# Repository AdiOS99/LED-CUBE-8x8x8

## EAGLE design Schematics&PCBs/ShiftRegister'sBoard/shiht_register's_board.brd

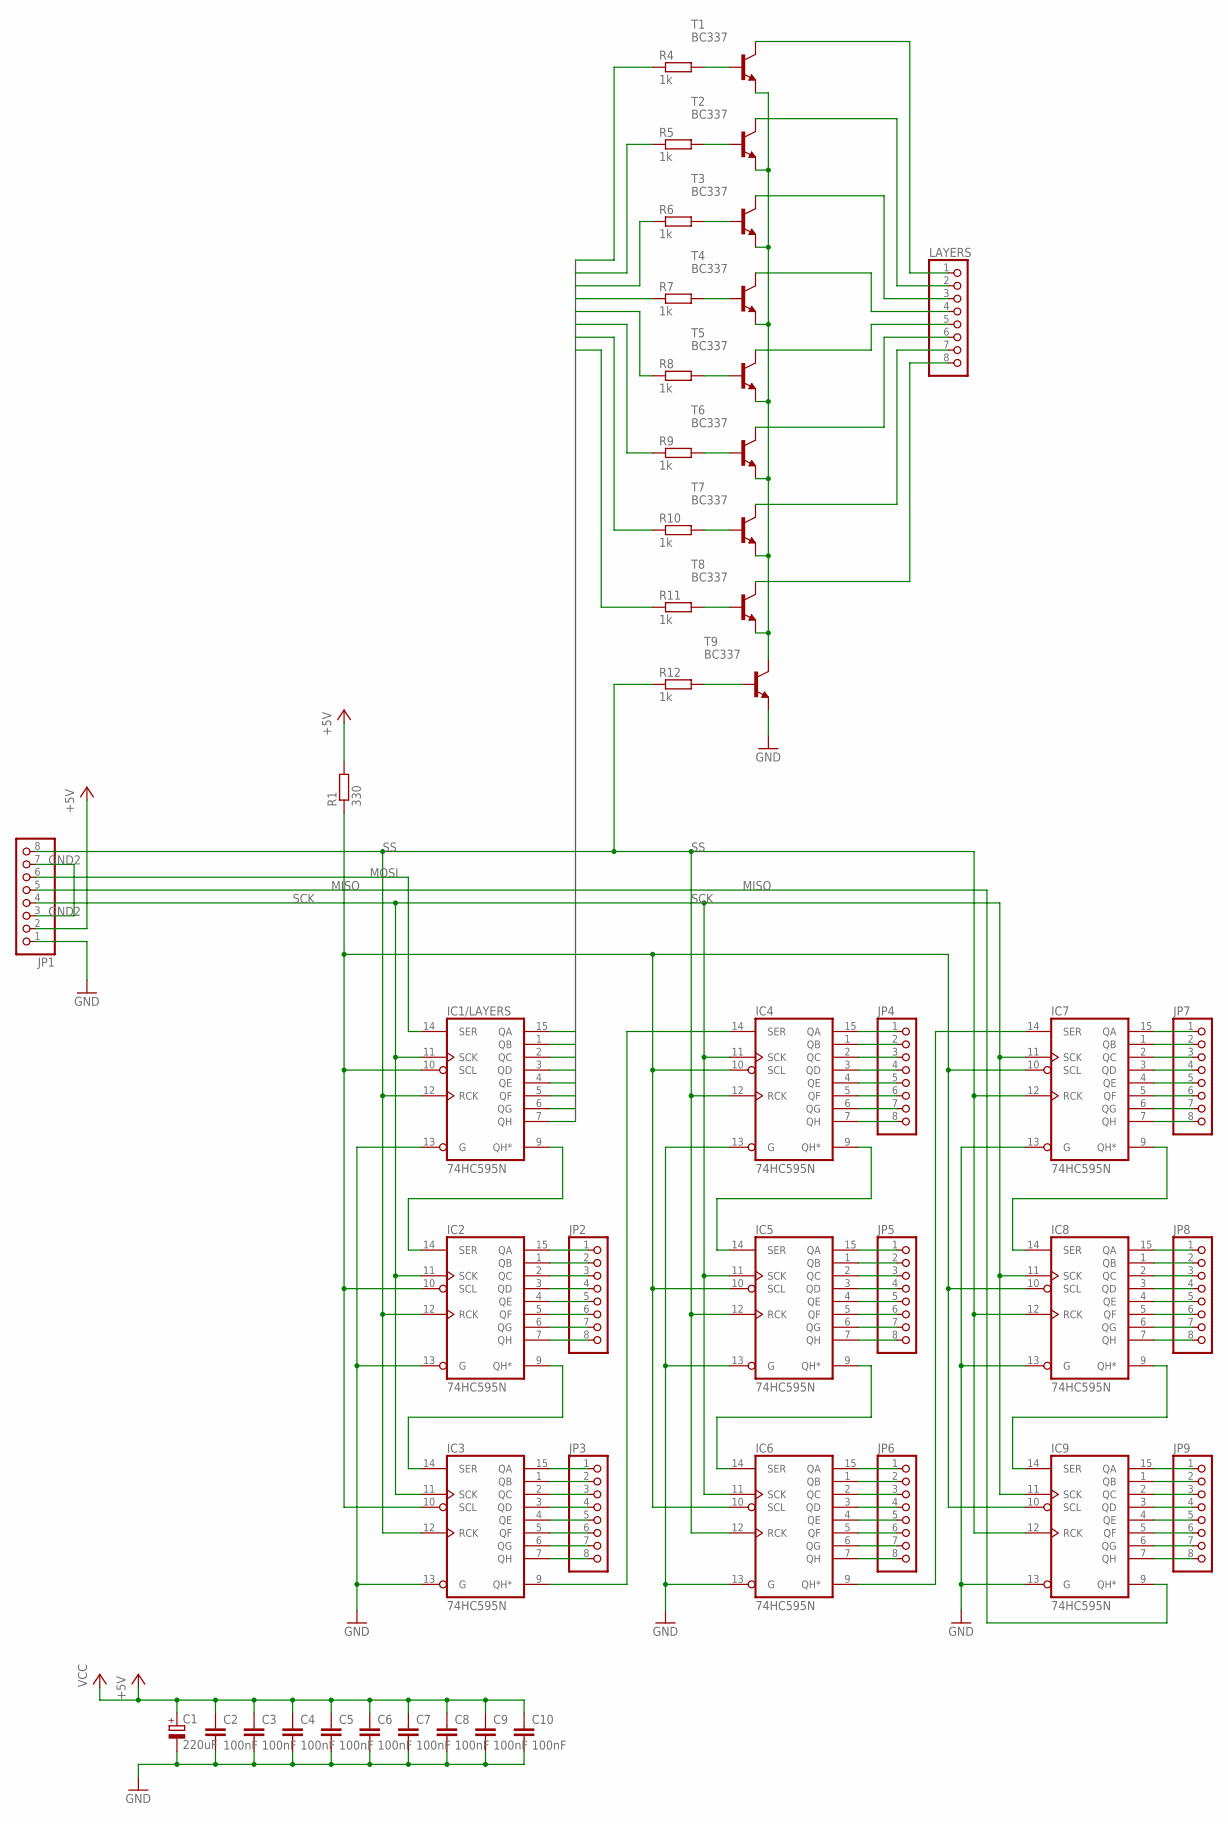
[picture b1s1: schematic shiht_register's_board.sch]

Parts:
C1: 220uF; E3,5-8
C2, C3, C4, C5, C6, C7, C8, C9, C10: 100nF; C025-025X050
IC1/LAYERS, IC2, IC3, IC4, IC5, IC6, IC7, IC8, IC9: 74HC595N; DIL16
JP1, JP2, JP3, JP4, JP5, JP6, JP7, JP8, JP9: PINHD-1X8; 1X08
LAYERS: PINHD-1X8; 1X08
R1: 330; 0207/2V
R4, R5, R6, R7, R8, R9, R10, R11, R12: 1k; 0207/2V
T1, T2, T3, T4, T5, T6, T7, T8, T9: BC337; TO92

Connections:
GND: C1.-, C2.2, C3.2, C4.2, C5.2, C6.2, C7.2, C8.2, C9.2, C10.2, IC1/LAYERS.8 (GND), IC1/LAYERS.13 (G), IC2.8 (GND), IC2.13 (G), IC3.8 (GND), IC3.13 (G), IC4.8 (GND), IC4.13 (G), IC5.8 (GND), IC5.13 (G), IC6.8 (GND), IC6.13 (G), IC7.8 (GND), IC7.13 (G), IC8.8 (GND), IC8.13 (G), IC9.8 (GND), IC9.13 (G), JP1.1, T9.1 (E)
GND2: JP1.3, JP1.7
LAYER1: IC1/LAYERS.15 (QA), R4.1
LAYER2: IC1/LAYERS.1 (QB), R5.1
LAYER3: IC1/LAYERS.2 (QC), R6.1
LAYER4: IC1/LAYERS.3 (QD), R7.1
LAYER5: IC1/LAYERS.4 (QE), R8.1
LAYER6: IC1/LAYERS.5 (QF), R9.1
LAYER7: IC1/LAYERS.6 (QG), R10.1
LAYER8: IC1/LAYERS.7 (QH), R11.1
MISO: IC9.9 (QH*), JP1.5
MOSI: IC1/LAYERS.14 (SER), JP1.6
unnamed: IC9.15 (QA), JP9.1
unnamed: IC9.1 (QB), JP9.2
unnamed: IC9.2 (QC), JP9.3
unnamed: IC9.3 (QD), JP9.4
unnamed: IC9.4 (QE), JP9.5
unnamed: IC9.5 (QF), JP9.6
unnamed: IC9.6 (QG), JP9.7
unnamed: IC9.7 (QH), JP9.8
unnamed: IC2.15 (QA), JP2.1
unnamed: IC2.1 (QB), JP2.2
unnamed: IC2.2 (QC), JP2.3
unnamed: IC2.3 (QD), JP2.4
unnamed: IC2.4 (QE), JP2.5
unnamed: IC2.5 (QF), JP2.6
unnamed: IC2.6 (QG), JP2.7
unnamed: IC2.7 (QH), JP2.8
unnamed: IC3.15 (QA), JP3.1
unnamed: IC3.1 (QB), JP3.2
unnamed: IC3.2 (QC), JP3.3
unnamed: IC3.3 (QD), JP3.4
unnamed: IC3.4 (QE), JP3.5
unnamed: IC3.5 (QF), JP3.6
unnamed: IC3.6 (QG), JP3.7
unnamed: IC3.7 (QH), JP3.8
unnamed: IC6.15 (QA), JP6.1
unnamed: IC6.1 (QB), JP6.2
unnamed: IC6.2 (QC), JP6.3
unnamed: IC6.3 (QD), JP6.4
unnamed: IC6.4 (QE), JP6.5
unnamed: IC6.5 (QF), JP6.6
unnamed: IC6.6 (QG), JP6.7
unnamed: IC6.7 (QH), JP6.8
unnamed: IC5.15 (QA), JP5.1
unnamed: IC5.1 (QB), JP5.2
unnamed: IC5.2 (QC), JP5.3
unnamed: IC5.3 (QD), JP5.4
unnamed: IC5.4 (QE), JP5.5
unnamed: IC5.5 (QF), JP5.6
unnamed: IC5.6 (QG), JP5.7
unnamed: IC5.7 (QH), JP5.8
unnamed: IC8.15 (QA), JP8.1
unnamed: IC8.1 (QB), JP8.2
unnamed: IC8.2 (QC), JP8.3
unnamed: IC8.3 (QD), JP8.4
unnamed: IC8.4 (QE), JP8.5
unnamed: IC8.5 (QF), JP8.6
unnamed: IC8.6 (QG), JP8.7
unnamed: IC8.7 (QH), JP8.8
unnamed: IC7.15 (QA), JP7.1
unnamed: IC7.1 (QB), JP7.2
unnamed: IC7.2 (QC), JP7.3
unnamed: IC7.3 (QD), JP7.4
unnamed: IC7.4 (QE), JP7.5
unnamed: IC7.5 (QF), JP7.6
unnamed: IC7.6 (QG), JP7.7
unnamed: IC7.7 (QH), JP7.8
unnamed: IC4.15 (QA), JP4.1
unnamed: IC4.1 (QB), JP4.2
unnamed: IC4.2 (QC), JP4.3
unnamed: IC4.3 (QD), JP4.4
unnamed: IC4.4 (QE), JP4.5
unnamed: IC4.5 (QF), JP4.6
unnamed: IC4.6 (QG), JP4.7
unnamed: IC4.7 (QH), JP4.8
unnamed: IC1/LAYERS.9 (QH*), IC2.14 (SER)
unnamed: IC2.9 (QH*), IC3.14 (SER)
unnamed: IC3.9 (QH*), IC4.14 (SER)
unnamed: IC4.9 (QH*), IC5.14 (SER)
unnamed: IC5.9 (QH*), IC6.14 (SER)
unnamed: IC6.9 (QH*), IC7.14 (SER)
unnamed: IC7.9 (QH*), IC8.14 (SER)
unnamed: IC8.9 (QH*), IC9.14 (SER)
unnamed: LAYERS.1, T1.3 (C)
unnamed: LAYERS.2, T2.3 (C)
unnamed: LAYERS.3, T3.3 (C)
unnamed: LAYERS.4, T4.3 (C)
unnamed: LAYERS.5, T5.3 (C)
unnamed: IC1/LAYERS.10 (SCL), IC2.10 (SCL), IC3.10 (SCL), IC4.10 (SCL), IC5.10 (SCL), IC6.10 (SCL), IC7.10 (SCL), IC8.10 (SCL), IC9.10 (SCL), R1.1
unnamed: LAYERS.6, T6.3 (C)
unnamed: LAYERS.7, T7.3 (C)
unnamed: LAYERS.8, T8.3 (C)
unnamed: T1.1 (E), T2.1 (E), T3.1 (E), T4.1 (E), T5.1 (E), T6.1 (E), T7.1 (E), T8.1 (E), T9.3 (C)
unnamed: R4.2, T1.2 (B)
unnamed: R5.2, T2.2 (B)
unnamed: R6.2, T3.2 (B)
unnamed: R7.2, T4.2 (B)
unnamed: R8.2, T5.2 (B)
unnamed: R9.2, T6.2 (B)
unnamed: R10.2, T7.2 (B)
unnamed: R11.2, T8.2 (B)
unnamed: R12.2, T9.2 (B)
SCK: IC1/LAYERS.11 (SCK), IC2.11 (SCK), IC3.11 (SCK), IC4.11 (SCK), IC5.11 (SCK), IC6.11 (SCK), IC7.11 (SCK), IC8.11 (SCK), IC9.11 (SCK), JP1.4
SS: IC1/LAYERS.12 (RCK), IC2.12 (RCK), IC3.12 (RCK), IC4.12 (RCK), IC5.12 (RCK), IC6.12 (RCK), IC7.12 (RCK), IC8.12 (RCK), IC9.12 (RCK), JP1.8, R12.1

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
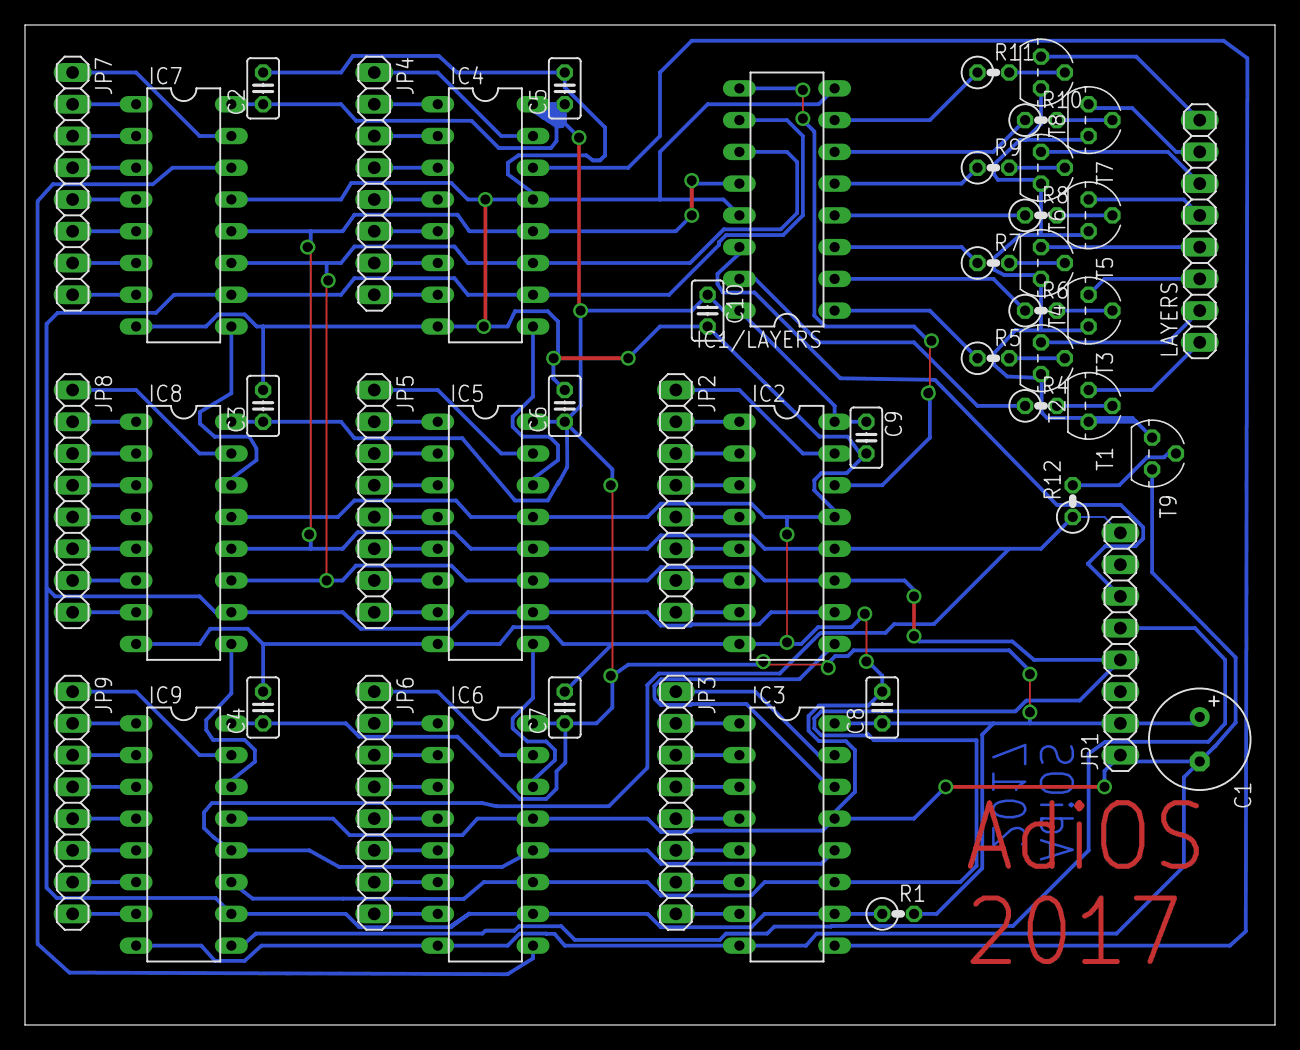
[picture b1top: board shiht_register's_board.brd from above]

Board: 2 copper layers, 100.0 x 80.0 mm, 48 parts (0 on the bottom side), 106 nets.

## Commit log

2017-10-13 Initial commit
    Load all data on GitHub
2017-10-13 Upload files
2017-10-13 Anims->functions
    Transfer animations from arrays to the functions
2017-10-13 Anims->Functions Complete
2017-10-13 Send datasheets
    Datasheet for:
    - Atmega32A
    - BC337
    - SN74HC595
2017-10-13 Schematics&PCBs
    Send shift register's board schematic and pcb
2018-07-18 Adding USART
    frame: 8bit + 2 stop bits
    BAUD 9600
    No checking frame errors
